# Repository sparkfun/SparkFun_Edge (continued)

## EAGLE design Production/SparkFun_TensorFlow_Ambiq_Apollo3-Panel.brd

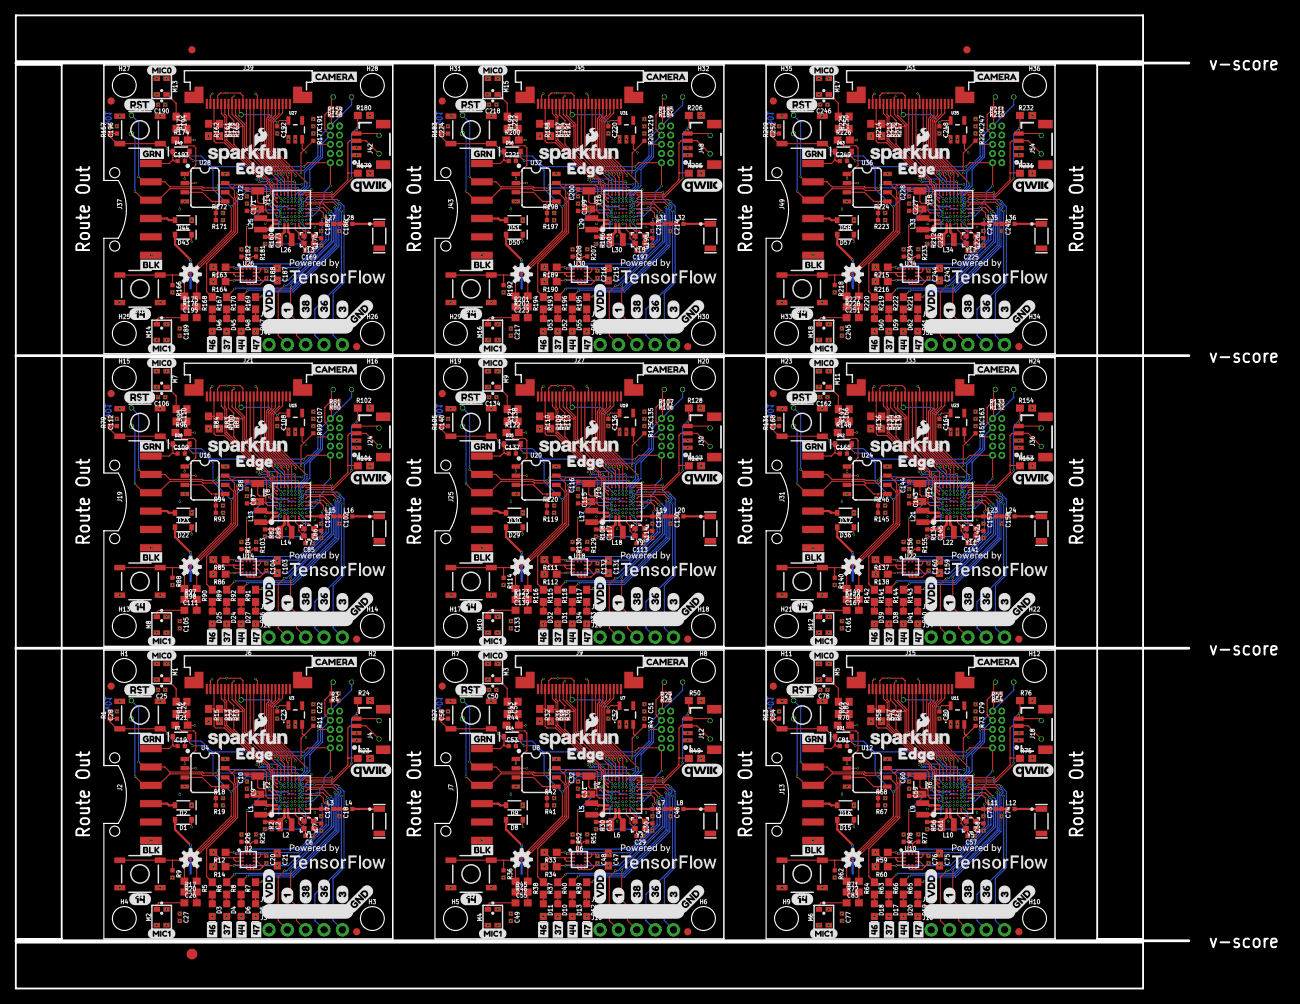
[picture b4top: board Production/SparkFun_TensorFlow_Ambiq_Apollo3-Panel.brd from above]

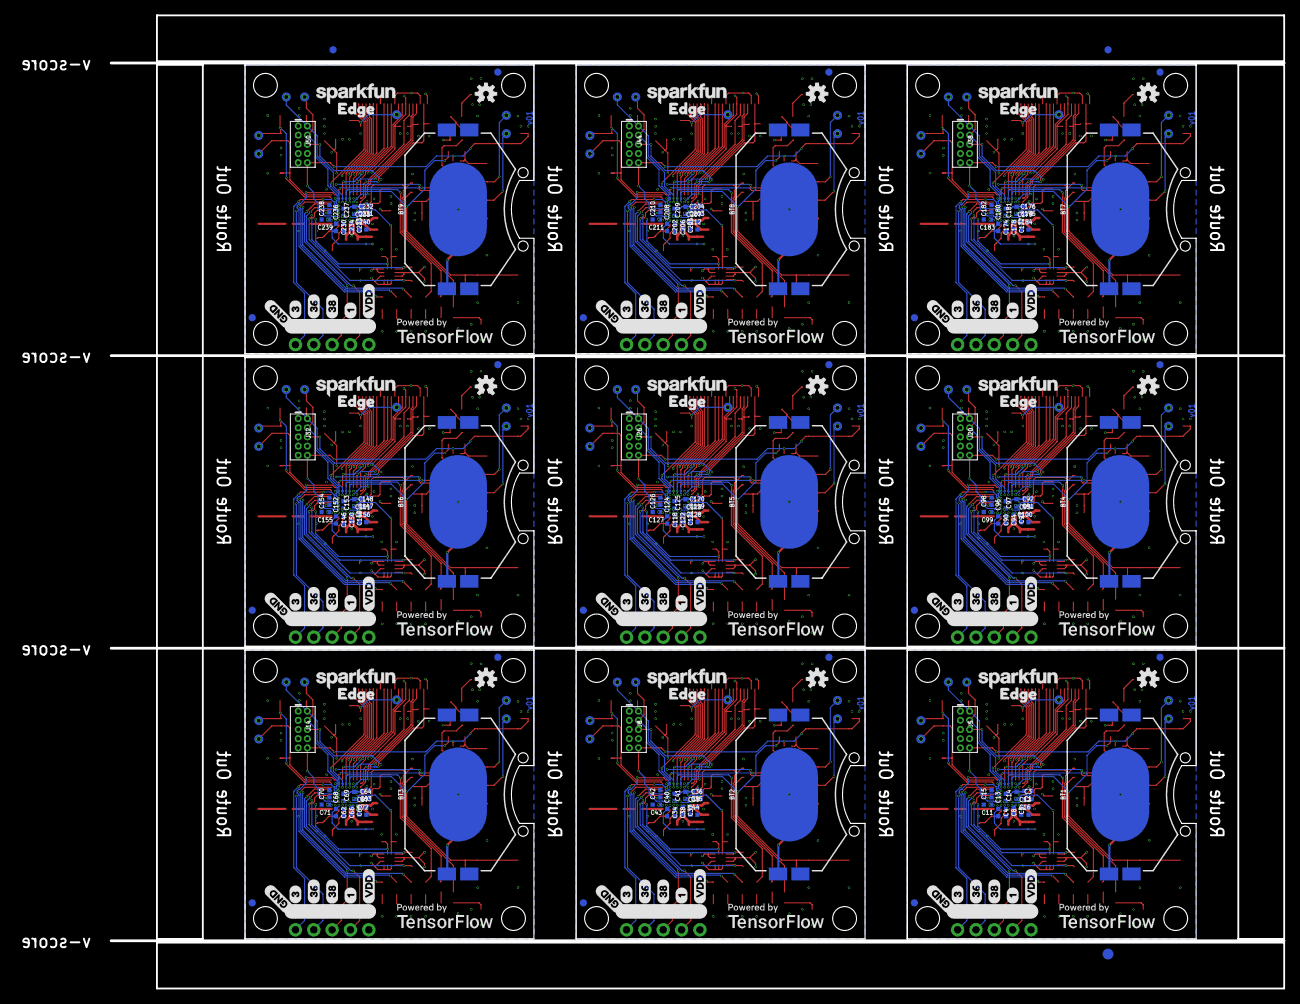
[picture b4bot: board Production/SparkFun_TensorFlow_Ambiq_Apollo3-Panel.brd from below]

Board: 4 copper layers, 162.4 x 134.7 mm, 1176 parts (291 on the bottom side), 666 nets.

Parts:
A1, A2, A3, A4, A5, A6, A7, A8, A9: 2.4GHZ-3.2X1.6MM; ANT-2.4GHZ-3.2X1.6X1.2MM
BT1, BT2, BT3, BT4, BT5, BT6, BT7, BT8, BT9: BATTCON_20MM_4LEGS_OVERPASTE_INNER
C1, C35, C63, C91, C119, C147, C175, C203, C231: 0.47uF; 0402-TIGHT
C2, C33, C61, C89, C117, C145, C173, C201, C229: 4.7uF; 0402-TIGHT
C3, C5, C8, C16, C36, C37, C38, C44, C64, C65, C66, C72, C92, C93, C94, C100, C120, C121, C122, C128, C148, C149, C150, C156, C176, C177, C178, C184, C204, C205, C206, C212, C232, C233, C234, C240: 2.2uF; 0402-TIGHT
C4, C12, C13, C14, C15, C22, C23, C34, C39, C40, C41, C42, C51, C52, C62, C67, C68, C69, C70, C79, C80, C90, C95, C96, C97, C98, C107, C108, C118, C123, C124, C125, C126, C135, C136, C146, C151, C152, C153, C154, C163, C164, C174, C179, C180, C181, C182, C191, C192, C202, C207, C208, C209, C210, C219, C220, C230, C235, C236, C237, C238, C247, C248: 1.0uF; 0402-TIGHT
C6, C7, C29, C30, C57, C58, C85, C86, C113, C114, C141, C142, C169, C170, C197, C198, C225, C226: 6pF; 0402-TIGHT
C9, C10, C31, C32, C59, C60, C87, C88, C115, C116, C143, C144, C171, C172, C199, C200, C227, C228: 15pF; 0402-TIGHT
C11, C43, C71, C99, C127, C155, C183, C211, C239: 47nF; 0402-TIGHT
C17, C45, C73, C101, C129, C157, C185, C213, C241: DNP; 0402-TIGHT
C18, C46, C74, C102, C130, C158, C186, C214, C242: 0.5pF; 0402-TIGHT
C19, C20, C25, C27, C48, C49, C50, C53, C76, C77, C78, C81, C104, C105, C106, C109, C132, C133, C134, C137, C160, C161, C162, C165, C188, C189, C190, C193, C216, C217, C218, C221, C244, C245, C246, C249: 0.1uF; 0402-TIGHT
C21, C47, C75, C103, C131, C159, C187, C215, C243: 10uF; 0603
C24, C26, C54, C55, C82, C83, C110, C111, C138, C139, C166, C167, C194, C195, C222, C223, C250, C251: 4.7uF; 0603
C28, C56, C84, C112, C140, C168, C196, C224, C252: 1.0nF; 0402-TIGHT
D1, D2, D8, D9, D15, D16, D22, D23, D29, D30, D36, D37, D43, D44, D50, D51, D57, D58: 1A/23V/620mV; SOD-323@1
D3, D11, D18, D25, D32, D39, D46, D53, D60: RED; LED-0603
D4, D10, D17, D24, D31, D38, D45, D52, D59: BLUE; LED-0603
D5, D12, D19, D26, D33, D40, D47, D54, D61: Yellow; LED-0603
D6, D13, D20, D27, D34, D41, D48, D55, D62: GREEN; LED-0603
D7, D14, D21, D28, D35, D42, D49, D56, D63: 250mA/100V; SOD-323
E$1, E$2, E$3, E$4: FIDUCIAL-1X2
E$5, E$6: FIDUCIAL-1.5X3
FD1, FD2, FD3, FD4, FD5, FD6, FD7, FD8, FD9, FD10, FD11, FD12, FD13, FD14, FD15, FD16, FD17, FD18, FD19, FD20, FD21, FD22, FD23, FD24, FD25, FD26, FD27, FD28, FD29, FD30, FD31, FD32, FD33, FD34, FD35, FD36: FIDUCIAL1X2; FIDUCIAL-1X2
H1, H2, H3, H4, H5, H6, H7, H8, H9, H10, H11, H12, H13, H14, H15, H16, H17, H18, H19, H20, H21, H22, H23, H24, H25, H26, H27, H28, H29, H30, H31, H32, H33, H34, H35, H36: STAND-OFF
J1, J3, J10, J11, J16, J17, J22, J23, J28, J29, J34, J35, J40, J41, J46, J47, J52, J53: 1X05_NO_SILK
J2, J7, J13, J19, J25, J31, J37, J43, J49: 1X06-SMD_RA_MALE
J4, J12, J18, J24, J30, J36, J42, J48, J54: 1X04_1MM_RA
J5, J8, J14, J20, J26, J32, J38, J44, J50: CORTEX_DEBUG_PTH; 2X5-PTH-1.27MM
J6, J9, J15, J21, J27, J33, J39, J45, J51: CAMERA-0V7670; FPC-24-AMPHENOL-SFV24R-1STE1HLF
L1, L5, L9, L13, L17, L21, L25, L29, L33: 2.2uH; 0805-WIDE
L2, L6, L10, L14, L18, L22, L26, L30, L34: 1.0uH; 0805-WIDE
L3, L7, L11, L15, L19, L23, L27, L31, L35: 2.7nH; 0402-TIGHT
L4, L8, L12, L16, L20, L24, L28, L32, L36: 2.0nH; 0402-TIGHT
LOGO1, LOGO3, LOGO5, LOGO7, LOGO9, LOGO11, LOGO13, LOGO15, LOGO17: SFE_LOGO_NAME_FLAME.1_INCH; SFE_LOGO_NAME_FLAME_.1
LOGO2, LOGO4, LOGO6, LOGO8, LOGO10, LOGO12, LOGO14, LOGO16, LOGO18: OSHW-LOGOS; OSHW-LOGO-S
M1, M2, M3, M4, M5, M6, M7, M8, M9, M10, M11, M12, M13, M14, M15, M16, M17, M18: MEMS_MIC; SPW2430HR5H-B
R1, R3, R4, R9, R10, R11, R19, R22, R25, R26, R27, R28, R29, R35, R36, R41, R47, R48, R51, R52, R53, R54, R55, R61, R62, R67, R73, R74, R77, R78, R79, R80, R81, R87, R88, R93, R99, R100, R103, R104, R105, R106, R107, R113, R114, R119, R125, R126, R129, R130, R131, R132, R133, R139, R140, R145, R151, R152, R155, R156, R157, R158, R159, R165, R166, R171, R177, R178, R181, R182, R183, R184, R185, R191, R192, R197, R203, R204, R207, R208, R209, R210, R211, R217, R218, R223, R229, R230, R233, R234: 10k; 0402-TIGHT
R2, R30, R56, R82, R108, R134, R160, R186, R212: 0; 0402-TIGHT
R5, R6, R7, R8, R37, R38, R39, R40, R63, R64, R65, R66, R89, R90, R91, R92, R115, R116, R117, R118, R141, R142, R143, R144, R167, R168, R169, R170, R193, R194, R195, R196, R219, R220, R221, R222: 1k; 0603
R12, R13, R14, R15, R23, R24, R31, R32, R33, R34, R49, R50, R57, R58, R59, R60, R75, R76, R83, R84, R85, R86, R101, R102, R109, R110, R111, R112, R127, R128, R135, R136, R137, R138, R153, R154, R161, R162, R163, R164, R179, R180, R187, R188, R189, R190, R205, R206, R213, R214, R215, R216, R231, R232: 4.7k; 0603
R16, R17, R43, R45, R69, R71, R95, R97, R121, R123, R147, R149, R173, R175, R199, R201, R225, R227: 10k; 0603
R18, R42, R68, R94, R120, R146, R172, R198, R224: 22k; 0402-TIGHT
R20, R21, R44, R46, R70, R72, R96, R98, R122, R124, R148, R150, R174, R176, R200, R202, R226, R228: 100k; 0603
S1, S2, S3, S4, S5, S6, S7, S8, S9, S10, S11, S12, S13, S14, S15, S16, S17, S18: TACTILE_SWITCH_SMD_5.2MM
TP1, TP2, TP3, TP4, TP5, TP6, TP7, TP8, TP9, TP10, TP11, TP12, TP13, TP14, TP15, TP16, TP17, TP18, TP19, TP20, TP21, TP22, TP23, TP24, TP25, TP26, TP27, TP28, TP29, TP30, TP31, TP32, TP33, TP34, TP35, TP36, TP37, TP38, TP39, TP40, TP41, TP42, TP43, TP44, TP45, TP46, TP47, TP48, TP49, TP50, TP51, TP52, TP53, TP54, TP55, TP56, TP57, TP58, TP59, TP60, TP61, TP62, TP63: TEST-POINT3X5; PAD.03X.05
U1, U5, U9, U13, U17, U21, U25, U29, U33: AMBIQ-APOLLO3KBR; BGA-81-5X5MM
U2, U6, U10, U14, U18, U22, U26, U30, U34: LIS2DH12; LGA-12-LISDH12
U3, U7, U11, U15, U19, U23, U27, U31, U35: 1.8V; SOT23-5
U4, U8, U12, U16, U20, U24, U28, U32, U36: LMV358; SO08
U$1, U$55, U$85, U$115, U$145, U$175, U$205, U$235, U$265: MIC00
U$2, U$41, U$71, U$101, U$131, U$161, U$191, U$221, U$251: BLK2
U$3, U$14, U$31, U$38, U$61, U$68, U$91, U$98, U$121, U$128, U$151, U$158, U$181, U$188, U$211, U$218, U$241, U$248: GND0
U$4, U$9, U$32, U$35, U$62, U$65, U$92, U$95, U$122, U$125, U$152, U$155, U$182, U$185, U$212, U$215, U$242, U$245: VDD1
U$5, U$8, U$43, U$44, U$73, U$74, U$103, U$104, U$133, U$134, U$163, U$164, U$193, U$194, U$223, U$224, U$253, U$254: 10
U$6, U$11, U$33, U$36, U$63, U$66, U$93, U$96, U$123, U$126, U$153, U$156, U$183, U$186, U$213, U$216, U$243, U$246: 383
U$7, U$12, U$34, U$37, U$64, U$67, U$94, U$97, U$124, U$127, U$154, U$157, U$184, U$187, U$214, U$217, U$244, U$247: 364
U$10, U$13, U$45, U$46, U$75, U$76, U$105, U$106, U$135, U$136, U$165, U$166, U$195, U$196, U$225, U$226, U$255, U$256: 31
U$15, U$47, U$77, U$107, U$137, U$167, U$197, U$227, U$257: 461
U$16, U$48, U$78, U$108, U$138, U$168, U$198, U$228, U$258: 372
U$17, U$49, U$79, U$109, U$139, U$169, U$199, U$229, U$259: 443
U$18, U$50, U$80, U$110, U$140, U$170, U$200, U$230, U$260: 470
U$19, U$51, U$81, U$111, U$141, U$171, U$201, U$231, U$261: QWIIC_COPYRIGHT_SMALL
U$20, U$52, U$82, U$112, U$142, U$172, U$202, U$232, U$262: CAMERA3
U$21, U$25, U$53, U$58, U$83, U$88, U$113, U$118, U$143, U$148, U$173, U$178, U$203, U$208, U$233, U$238, U$263, U$268: POWEREDBY_TF#JPG
U$22, U$56, U$86, U$116, U$146, U$176, U$206, U$236, U$266: MIC11
U$23, U$24, U$54, U$57, U$84, U$87, U$114, U$117, U$144, U$147, U$174, U$177, U$204, U$207, U$234, U$237, U$264, U$267: EDGE0
U$26, U$39, U$69, U$99, U$129, U$159, U$189, U$219, U$249: 1416
U$27, U$40, U$70, U$100, U$130, U$160, U$190, U$220, U$250: RST15
U$28, U$42, U$72, U$102, U$132, U$162, U$192, U$222, U$252: GRN1
U$29, U$59, U$89, U$119, U$149, U$179, U$209, U$239, U$269: SFE_LOGO_NAME_.1
U$30, U$60, U$90, U$120, U$150, U$180, U$210, U$240, U$270: OSHW-LOGO-S
Y1, Y3, Y5, Y7, Y9, Y11, Y13, Y15, Y17: 32MHz; CRYSTAL-SMD-2.0X1.6MM
Y2, Y4, Y6, Y8, Y10, Y12, Y14, Y16, Y18: 32.768kHz; CRYSTAL-SMD-3.2X1.5MM

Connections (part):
1.8V: C23.1, J6.10, TP7.P$1, U3.5
1.8V1: C52.1, J9.10, TP14.P$1, U7.5
1.8V2: C80.1, J15.10, TP21.P$1, U11.5
1.8V3: C108.1, J21.10, TP28.P$1, U15.5
1.8V4: C136.1, J27.10, TP35.P$1, U19.5
1.8V5: C164.1, J33.10, TP42.P$1, U23.5
1.8V6: C192.1, J39.10, TP49.P$1, U27.5
1.8V7: C220.1, J45.10, TP56.P$1, U31.5
1.8V8: C248.1, J51.10, TP63.P$1, U35.5
ADC_VREF: C1.1, U1.A6
ADC_VREF1: C35.1, U5.A6
ADC_VREF2: C63.1, U9.A6
ADC_VREF3: C91.1, U13.A6
ADC_VREF4: C119.1, U17.A6
ADC_VREF5: C147.1, U21.A6
ADC_VREF6: C175.1, U25.A6
ADC_VREF7: C203.1, U29.A6
ADC_VREF8: C231.1, U33.A6
AMBIQ_!RST: C19.2, C28.1, J5.10, R1.1, S2.3, S2.4, U1.G3
AMBIQ_!RST1: C53.2, C56.1, J8.10, R27.1, S4.3, S4.4, U5.G3
AMBIQ_!RST2: C81.2, C84.1, J14.10, R53.1, S6.3, S6.4, U9.G3
AMBIQ_!RST3: C109.2, C112.1, J20.10, R79.1, S8.3, S8.4, U13.G3
AMBIQ_!RST4: C137.2, C140.1, J26.10, R105.1, S10.3, S10.4, U17.G3
AMBIQ_!RST5: C165.2, C168.1, J32.10, R131.1, S12.3, S12.4, U21.G3
AMBIQ_!RST6: C193.2, C196.1, J38.10, R157.1, S14.3, S14.4, U25.G3
AMBIQ_!RST7: C221.2, C224.1, J44.10, R183.1, S16.3, S16.4, U29.G3
AMBIQ_!RST8: C249.2, C252.1, J50.10, R209.1, S18.3, S18.4, U33.G3
DTR: C19.1, D7.C, J2.1
DTR1: C53.1, D14.C, J7.1
DTR2: C81.1, D21.C, J13.1
DTR3: C109.1, D28.C, J19.1
DTR4: C137.1, D35.C, J25.1
DTR5: C165.1, D42.C, J31.1
DTR6: C193.1, D49.C, J37.1
DTR7: C221.1, D56.C, J43.1
DTR8: C249.1, D63.C, J49.1
DVDD: C11.1, U1.H3
DVDD1: C43.1, U5.H3
DVDD2: C71.1, U9.H3
DVDD3: C99.1, U13.H3
DVDD4: C127.1, U17.H3
DVDD5: C155.1, U21.H3
DVDD6: C183.1, U25.H3
DVDD7: C211.1, U29.H3
DVDD8: C239.1, U33.H3
FTDI_VCC: D2.A, J2.4
FTDI_VCC1: D9.A, J7.4
FTDI_VCC2: D16.A, J13.4
FTDI_VCC3: D23.A, J19.4
FTDI_VCC4: D30.A, J25.4
FTDI_VCC5: D37.A, J31.4
FTDI_VCC6: D44.A, J37.4
FTDI_VCC7: D51.A, J43.4
FTDI_VCC8: D58.A, J49.4
GND: BT1.2, C1.2, C2.2, C3.2, C4.2, C5.2, C6.1, C7.1, C8.2, C9.1, C10.1, C11.2, C12.2, C13.2, C14.2, C15.2, C16.2, C17.2, C18.2, C20.2, C21.2, C22.2, C23.2, C25.2, C27.2, C28.2, D3.C, D4.C, D5.C, D6.C, J1.1, J1.2, J1.3, J1.4, J1.5, J2.6, J4.1, J5.3, J5.5, J5.9, J6.2, J6.15, M1.2, M1.3, M2.2, M2.3, R4.1, R11.1, R19.1, R22.1, S1.1, S1.2, S2.1, S2.2, U1.B3, U1.C2, U1.E2, U1.E3, U1.F2, U1.H1, U1.H2, U1.J2, U2.5, U2.6, U2.7, U2.8, U3.2, U4.4
GND1: BT2.2, C29.1, C30.1, C31.1, C32.1, C33.2, C34.2, C35.2, C36.2, C37.2, C38.2, C39.2, C40.2, C41.2, C42.2, C43.2, C44.2, C45.2, C46.2, C47.2, C48.2, C49.2, C50.2, C51.2, C52.2, C56.2, D10.C, D11.C, D12.C, D13.C, J7.6, J8.3, J8.5, J8.9, J9.2, J9.15, J11.1, J11.2, J11.3, J11.4, J11.5, J12.1, M3.2, M3.3, M4.2, M4.3, R28.1, R41.1, R47.1, R48.1, S3.1, S3.2, S4.1, S4.2, U5.B3, U5.C2, U5.E2, U5.E3, U5.F2, U5.H1, U5.H2, U5.J2, U6.5, U6.6, U6.7, U6.8, U7.2, U8.4
GND2: BT3.2, C57.1, C58.1, C59.1, C60.1, C61.2, C62.2, C63.2, C64.2, C65.2, C66.2, C67.2, C68.2, C69.2, C70.2, C71.2, C72.2, C73.2, C74.2, C75.2, C76.2, C77.2, C78.2, C79.2, C80.2, C84.2, D17.C, D18.C, D19.C, D20.C, J13.6, J14.3, J14.5, J14.9, J15.2, J15.15, J17.1, J17.2, J17.3, J17.4, J17.5, J18.1, M5.2, M5.3, M6.2, M6.3, R54.1, R67.1, R73.1, R74.1, S5.1, S5.2, S6.1, S6.2, U9.B3, U9.C2, U9.E2, U9.E3, U9.F2, U9.H1, U9.H2, U9.J2, U10.5, U10.6, U10.7, U10.8, U11.2, U12.4
GND3: BT4.2, C85.1, C86.1, C87.1, C88.1, C89.2, C90.2, C91.2, C92.2, C93.2, C94.2, C95.2, C96.2, C97.2, C98.2, C99.2, C100.2, C101.2, C102.2, C103.2, C104.2, C105.2, C106.2, C107.2, C108.2, C112.2, D24.C, D25.C, D26.C, D27.C, J19.6, J20.3, J20.5, J20.9, J21.2, J21.15, J23.1, J23.2, J23.3, J23.4, J23.5, J24.1, M7.2, M7.3, M8.2, M8.3, R80.1, R93.1, R99.1, R100.1, S7.1, S7.2, S8.1, S8.2, U13.B3, U13.C2, U13.E2, U13.E3, U13.F2, U13.H1, U13.H2, U13.J2, U14.5, U14.6, U14.7, U14.8, U15.2, U16.4
GND4: BT5.2, C113.1, C114.1, C115.1, C116.1, C117.2, C118.2, C119.2, C120.2, C121.2, C122.2, C123.2, C124.2, C125.2, C126.2, C127.2, C128.2, C129.2, C130.2, C131.2, C132.2, C133.2, C134.2, C135.2, C136.2, C140.2, D31.C, D32.C, D33.C, D34.C, J25.6, J26.3, J26.5, J26.9, J27.2, J27.15, J29.1, J29.2, J29.3, J29.4, J29.5, J30.1, M9.2, M9.3, M10.2, M10.3, R106.1, R119.1, R125.1, R126.1, S9.1, S9.2, S10.1, S10.2, U17.B3, U17.C2, U17.E2, U17.E3, U17.F2, U17.H1, U17.H2, U17.J2, U18.5, U18.6, U18.7, U18.8, U19.2, U20.4
GND5: BT6.2, C141.1, C142.1, C143.1, C144.1, C145.2, C146.2, C147.2, C148.2, C149.2, C150.2, C151.2, C152.2, C153.2, C154.2, C155.2, C156.2, C157.2, C158.2, C159.2, C160.2, C161.2, C162.2, C163.2, C164.2, C168.2, D38.C, D39.C, D40.C, D41.C, J31.6, J32.3, J32.5, J32.9, J33.2, J33.15, J35.1, J35.2, J35.3, J35.4, J35.5, J36.1, M11.2, M11.3, M12.2, M12.3, R132.1, R145.1, R151.1, R152.1, S11.1, S11.2, S12.1, S12.2, U21.B3, U21.C2, U21.E2, U21.E3, U21.F2, U21.H1, U21.H2, U21.J2, U22.5, U22.6, U22.7, U22.8, U23.2, U24.4
GND6: BT7.2, C169.1, C170.1, C171.1, C172.1, C173.2, C174.2, C175.2, C176.2, C177.2, C178.2, C179.2, C180.2, C181.2, C182.2, C183.2, C184.2, C185.2, C186.2, C187.2, C188.2, C189.2, C190.2, C191.2, C192.2, C196.2, D45.C, D46.C, D47.C, D48.C, J37.6, J38.3, J38.5, J38.9, J39.2, J39.15, J41.1, J41.2, J41.3, J41.4, J41.5, J42.1, M13.2, M13.3, M14.2, M14.3, R158.1, R171.1, R177.1, R178.1, S13.1, S13.2, S14.1, S14.2, U25.B3, U25.C2, U25.E2, U25.E3, U25.F2, U25.H1, U25.H2, U25.J2, U26.5, U26.6, U26.7, U26.8, U27.2, U28.4
GND7: BT8.2, C197.1, C198.1, C199.1, C200.1, C201.2, C202.2, C203.2, C204.2, C205.2, C206.2, C207.2, C208.2, C209.2, C210.2, C211.2, C212.2, C213.2, C214.2, C215.2, C216.2, C217.2, C218.2, C219.2, C220.2, C224.2, D52.C, D53.C, D54.C, D55.C, J43.6, J44.3, J44.5, J44.9, J45.2, J45.15, J47.1, J47.2, J47.3, J47.4, J47.5, J48.1, M15.2, M15.3, M16.2, M16.3, R184.1, R197.1, R203.1, R204.1, S15.1, S15.2, S16.1, S16.2, U29.B3, U29.C2, U29.E2, U29.E3, U29.F2, U29.H1, U29.H2, U29.J2, U30.5, U30.6, U30.7, U30.8, U31.2, U32.4
GND8: BT9.2, C225.1, C226.1, C227.1, C228.1, C229.2, C230.2, C231.2, C232.2, C233.2, C234.2, C235.2, C236.2, C237.2, C238.2, C239.2, C240.2, C241.2, C242.2, C243.2, C244.2, C245.2, C246.2, C247.2, C248.2, C252.2, D59.C, D60.C, D61.C, D62.C, J49.6, J50.3, J50.5, J50.9, J51.2, J51.15, J53.1, J53.2, J53.3, J53.4, J53.5, J54.1, M17.2, M17.3, M18.2, M18.3, R210.1, R223.1, R229.1, R230.1, S17.1, S17.2, S18.1, S18.2, U33.B3, U33.C2, U33.E2, U33.E3, U33.F2, U33.H1, U33.H2, U33.J2, U34.5, U34.6, U34.7, U34.8, U35.2, U36.4
GPIO0/ACCEL_INT1: R51.2, U5.H4, U6.11
GPIO0/ACCEL_INT2: R25.2, U1.H4, U2.11
GPIO0/ACCEL_INT3: R77.2, U9.H4, U10.11
GPIO0/ACCEL_INT4: R103.2, U13.H4, U14.11
GPIO0/ACCEL_INT5: R129.2, U17.H4, U18.11
GPIO0/ACCEL_INT6: R155.2, U21.H4, U22.11
GPIO0/ACCEL_INT7: R181.2, U25.H4, U26.11
GPIO0/ACCEL_INT8: R207.2, U29.H4, U30.11
GPIO0/ACCEL_INT9: R233.2, U33.H4, U34.11
GPIO1_J3_1: J10.2, U5.G4
GPIO1_J3_2: J3.2, U1.G4
GPIO1_J3_3: J16.2, U9.G4
GPIO1_J3_4: J22.2, U13.G4
GPIO1_J3_5: J28.2, U17.G4
GPIO1_J3_6: J34.2, U21.G4
GPIO1_J3_7: J40.2, U25.G4
GPIO1_J3_8: J46.2, U29.G4
GPIO1_J3_9: J52.2, U33.G4
GPIO3_J3_1: J10.5, U5.G5
GPIO3_J3_2: J16.5, U9.G5
GPIO3_J3_3: J22.5, U13.G5
GPIO3_J3_4: J28.5, U17.G5
GPIO3_J3_5: J3.5, U1.G5
GPIO3_J3_6: J34.5, U21.G5
GPIO3_J3_7: J40.5, U25.G5
GPIO3_J3_8: J46.5, U29.G5
GPIO3_J3_9: J52.5, U33.G5
GPIO4/CAMERA_Y1: J9.18, U5.D9
GPIO4/CAMERA_Y2: J15.18, U9.D9
GPIO4/CAMERA_Y3: J21.18, U13.D9
GPIO4/CAMERA_Y4: J6.18, U1.D9
GPIO4/CAMERA_Y5: J27.18, U17.D9
GPIO4/CAMERA_Y6: J33.18, U21.D9
GPIO4/CAMERA_Y7: J39.18, U25.D9
GPIO4/CAMERA_Y8: J45.18, U29.D9
GPIO4/CAMERA_Y9: J51.18, U33.D9
GPIO5/CAMERA_Y1: J9.20, U5.E9
GPIO5/CAMERA_Y2: J15.20, U9.E9
GPIO5/CAMERA_Y3: J6.20, U1.E9
GPIO5/CAMERA_Y4: J21.20, U13.E9
GPIO5/CAMERA_Y5: J27.20, U17.E9
GPIO5/CAMERA_Y6: J33.20, U21.E9
GPIO5/CAMERA_Y7: J39.20, U25.E9
GPIO5/CAMERA_Y8: J45.20, U29.E9
GPIO5/CAMERA_Y9: J51.20, U33.E9
GPIO6/CAMERA_Y0: J6.19, U1.E8
GPIO6/CAMERA_Y1: J9.19, U5.E8
GPIO6/CAMERA_Y2: J15.19, U9.E8
GPIO6/CAMERA_Y3: J21.19, U13.E8
GPIO6/CAMERA_Y4: J27.19, U17.E8
GPIO6/CAMERA_Y5: J33.19, U21.E8
GPIO6/CAMERA_Y6: J39.19, U25.E8
GPIO6/CAMERA_Y7: J45.19, U29.E8
GPIO6/CAMERA_Y8: J51.19, U33.E8
GPIO7/CAM_XCLK: J6.13, U1.F9
GPIO7/CAM_XCLK1: J9.13, U5.F9
GPIO7/CAM_XCLK2: J15.13, U9.F9
GPIO7/CAM_XCLK3: J21.13, U13.F9
GPIO7/CAM_XCLK4: J27.13, U17.F9
GPIO7/CAM_XCLK5: J33.13, U21.F9
GPIO7/CAM_XCLK6: J39.13, U25.F9
GPIO7/CAM_XCLK7: J45.13, U29.F9
GPIO7/CAM_XCLK8: J51.13, U33.F9
GPIO8/CAMERA_Y1: J6.21, U1.F8
GPIO8/CAMERA_Y2: J9.21, U5.F8
GPIO8/CAMERA_Y3: J15.21, U9.F8
GPIO8/CAMERA_Y4: J21.21, U13.F8
GPIO8/CAMERA_Y5: J27.21, U17.F8
GPIO8/CAMERA_Y6: J33.21, U21.F8
GPIO8/CAMERA_Y7: J39.21, U25.F8
GPIO8/CAMERA_Y8: J45.21, U29.F8
GPIO8/CAMERA_Y9: J51.21, U33.F8
GPIO9/CAMERA_Y1: J9.22, U5.G7
GPIO9/CAMERA_Y2: J6.22, U1.G7
GPIO9/CAMERA_Y3: J15.22, U9.G7
GPIO9/CAMERA_Y4: J21.22, U13.G7
GPIO9/CAMERA_Y5: J27.22, U17.G7
GPIO9/CAMERA_Y6: J33.22, U21.G7
GPIO9/CAMERA_Y7: J39.22, U25.G7
GPIO9/CAMERA_Y8: J45.22, U29.G7
GPIO9/CAMERA_Y9: J51.22, U33.G7
GPIO10/CAMERA_DVDD_EN: R11.2, U1.G8, U3.3
GPIO10/CAMERA_DVDD_EN1: R47.2, U5.G8, U7.3
GPIO10/CAMERA_DVDD_EN2: R73.2, U9.G8, U11.3
GPIO10/CAMERA_DVDD_EN3: R99.2, U13.G8, U15.3
GPIO10/CAMERA_DVDD_EN4: R125.2, U17.G8, U19.3
GPIO10/CAMERA_DVDD_EN5: R151.2, U21.G8, U23.3
GPIO10/CAMERA_DVDD_EN6: R177.2, U25.G8, U27.3
GPIO10/CAMERA_DVDD_EN7: R203.2, U29.G8, U31.3
GPIO10/CAMERA_DVDD_EN8: R229.2, U33.G8, U35.3
GPIO11/MIC0: R21.1, U1.B5, U4.1
GPIO11/MIC1: R44.1, U5.B5, U8.1
GPIO11/MIC2: R70.1, U9.B5, U12.1
GPIO11/MIC3: R96.1, U13.B5, U16.1
GPIO11/MIC4: R122.1, U17.B5, U20.1
GPIO11/MIC5: R148.1, U21.B5, U24.1
GPIO11/MIC6: R174.1, U25.B5, U28.1
GPIO11/MIC7: R200.1, U29.B5, U32.1
GPIO11/MIC8: R226.1, U33.B5, U36.1
GPIO12/CAMERA_VSYNC: J6.7, U1.A7
GPIO12/CAMERA_VSYNC1: J9.7, U5.A7
GPIO12/CAMERA_VSYNC2: J15.7, U9.A7
GPIO12/CAMERA_VSYNC3: J21.7, U13.A7
GPIO12/CAMERA_VSYNC4: J27.7, U17.A7
GPIO12/CAMERA_VSYNC5: J33.7, U21.A7
GPIO12/CAMERA_VSYNC6: J39.7, U25.A7
GPIO12/CAMERA_VSYNC7: J45.7, U29.A7
GPIO12/CAMERA_VSYNC8: J51.7, U33.A7
GPIO13/CAMERA_PWDN: J6.8, R22.2, U1.B7
GPIO13/CAMERA_PWDN1: J9.8, R48.2, U5.B7
GPIO13/CAMERA_PWDN2: J15.8, R74.2, U9.B7
GPIO13/CAMERA_PWDN3: J21.8, R100.2, U13.B7
GPIO13/CAMERA_PWDN4: J27.8, R126.2, U17.B7
GPIO13/CAMERA_PWDN5: J33.8, R152.2, U21.B7
GPIO13/CAMERA_PWDN6: J39.8, R178.2, U25.B7
GPIO13/CAMERA_PWDN7: J45.8, R204.2, U29.B7
GPIO13/CAMERA_PWDN8: J51.8, R230.2, U33.B7
GPIO14/USER_BUTTON: D7.A, R9.1, S1.3, S1.4, U1.D7
GPIO14/USER_BUTTON1: D14.A, R36.1, S3.3, S3.4, U5.D7
GPIO14/USER_BUTTON2: D21.A, R62.1, S5.3, S5.4, U9.D7
GPIO14/USER_BUTTON3: D28.A, R88.1, S7.3, S7.4, U13.D7
GPIO14/USER_BUTTON4: D35.A, R114.1, S9.3, S9.4, U17.D7
GPIO14/USER_BUTTON5: D42.A, R140.1, S11.3, S11.4, U21.D7
GPIO14/USER_BUTTON6: D49.A, R166.1, S13.3, S13.4, U25.D7
GPIO14/USER_BUTTON7: D56.A, R192.1, S15.3, S15.4, U29.D7
GPIO14/USER_BUTTON8: D63.A, R218.1, S17.3, S17.4, U33.D7
GPIO15/CAMERA_RESET: J6.6, R10.1, U1.C7
GPIO15/CAMERA_RESET1: J9.6, R35.1, U5.C7
GPIO15/CAMERA_RESET2: J15.6, R61.1, U9.C7
GPIO15/CAMERA_RESET3: J21.6, R87.1, U13.C7
GPIO15/CAMERA_RESET4: J27.6, R113.1, U17.C7
GPIO15/CAMERA_RESET5: J33.6, R139.1, U21.C7
GPIO15/CAMERA_RESET6: J39.6, R165.1, U25.C7
GPIO15/CAMERA_RESET7: J45.6, R191.1, U29.C7
GPIO15/CAMERA_RESET8: J51.6, R217.1, U33.C7
GPIO17/ACCEL_INT1: R26.2, U1.D3, U2.12
GPIO17/ACCEL_INT2: R52.2, U5.D3, U6.12
GPIO17/ACCEL_INT3: R78.2, U9.D3, U10.12
GPIO17/ACCEL_INT4: R104.2, U13.D3, U14.12
GPIO17/ACCEL_INT5: R130.2, U17.D3, U18.12
GPIO17/ACCEL_INT6: R156.2, U21.D3, U22.12
GPIO17/ACCEL_INT7: R182.2, U25.D3, U26.12
GPIO17/ACCEL_INT8: R208.2, U29.D3, U30.12
GPIO17/ACCEL_INT9: R234.2, U33.D3, U34.12
GPIO20/SWDCK: J5.4, R4.2, TP1.P$1, U1.G6
GPIO20/SWDCK1: J8.4, R28.2, TP8.P$1, U5.G6
GPIO20/SWDCK2: J14.4, R54.2, TP15.P$1, U9.G6
GPIO20/SWDCK3: J20.4, R80.2, TP22.P$1, U13.G6
GPIO20/SWDCK4: J26.4, R106.2, TP29.P$1, U17.G6
GPIO20/SWDCK5: J32.4, R132.2, TP36.P$1, U21.G6
GPIO20/SWDCK6: J38.4, R158.2, TP43.P$1, U25.G6
GPIO20/SWDCK7: J44.4, R184.2, TP50.P$1, U29.G6
GPIO20/SWDCK8: J50.4, R210.2, TP57.P$1, U33.G6
GPIO21/SWDIO: J5.2, R3.1, TP2.P$1, U1.F7
GPIO21/SWDIO1: J8.2, R29.1, TP9.P$1, U5.F7
GPIO21/SWDIO2: J14.2, R55.1, TP16.P$1, U9.F7
GPIO21/SWDIO3: J20.2, R81.1, TP23.P$1, U13.F7
GPIO21/SWDIO4: J26.2, R107.1, TP30.P$1, U17.F7
GPIO21/SWDIO5: J32.2, R133.1, TP37.P$1, U21.F7
GPIO21/SWDIO6: J38.2, R159.1, TP44.P$1, U25.F7
GPIO21/SWDIO7: J44.2, R185.1, TP51.P$1, U29.F7
GPIO21/SWDIO8: J50.2, R211.1, TP58.P$1, U33.F7
GPIO22/CAMERA_Y1: J9.16, U5.C9
GPIO22/CAMERA_Y2: J15.16, U9.C9
GPIO22/CAMERA_Y3: J21.16, U13.C9
GPIO22/CAMERA_Y4: J27.16, U17.C9
GPIO22/CAMERA_Y5: J6.16, U1.C9
GPIO22/CAMERA_Y6: J33.16, U21.C9
GPIO22/CAMERA_Y7: J39.16, U25.C9
GPIO22/CAMERA_Y8: J45.16, U29.C9
GPIO22/CAMERA_Y9: J51.16, U33.C9
GPIO23/CAMERA_PCLK: J6.17, U1.D8
GPIO23/CAMERA_PCLK1: J9.17, U5.D8
GPIO23/CAMERA_PCLK2: J15.17, U9.D8
GPIO23/CAMERA_PCLK3: J21.17, U13.D8
GPIO23/CAMERA_PCLK4: J27.17, U17.D8
GPIO23/CAMERA_PCLK5: J33.17, U21.D8
GPIO23/CAMERA_PCLK6: J39.17, U25.D8
GPIO23/CAMERA_PCLK7: J45.17, U29.D8
GPIO23/CAMERA_PCLK8: J51.17, U33.D8
GPIO24/CAMERA_Y1: J9.14, U5.C8
GPIO24/CAMERA_Y2: J15.14, U9.C8
GPIO24/CAMERA_Y3: J21.14, U13.C8
GPIO24/CAMERA_Y4: J27.14, U17.C8
GPIO24/CAMERA_Y5: J33.14, U21.C8
GPIO24/CAMERA_Y6: J6.14, U1.C8
GPIO24/CAMERA_Y7: J39.14, U25.C8
GPIO24/CAMERA_Y8: J45.14, U29.C8
GPIO24/CAMERA_Y9: J51.14, U33.C8
GPIO25/I2C_SDA_CAMERA: J6.3, R15.1, U1.A8
GPIO25/I2C_SDA_CAMERA1: J9.3, R32.1, U5.A8
GPIO25/I2C_SDA_CAMERA2: J15.3, R58.1, U9.A8
GPIO25/I2C_SDA_CAMERA3: J21.3, R84.1, U13.A8
GPIO25/I2C_SDA_CAMERA4: J27.3, R110.1, U17.A8
GPIO25/I2C_SDA_CAMERA5: J33.3, R136.1, U21.A8
GPIO25/I2C_SDA_CAMERA6: J39.3, R162.1, U25.A8
GPIO25/I2C_SDA_CAMERA7: J45.3, R188.1, U29.A8
GPIO25/I2C_SDA_CAMERA8: J51.3, R214.1, U33.A8
GPIO26/CAMERA_HREF: J6.9, U1.B8
GPIO26/CAMERA_HREF1: J9.9, U5.B8
GPIO26/CAMERA_HREF2: J15.9, U9.B8
GPIO26/CAMERA_HREF3: J21.9, U13.B8
GPIO26/CAMERA_HREF4: J27.9, U17.B8
GPIO26/CAMERA_HREF5: J33.9, U21.B8
GPIO26/CAMERA_HREF6: J39.9, U25.B8
GPIO26/CAMERA_HREF7: J45.9, U29.B8
GPIO26/CAMERA_HREF8: J51.9, U33.B8
GPIO27/I2C_SCL_CAMERA: J6.5, R13.1, U1.B9
GPIO27/I2C_SCL_CAMERA1: J9.5, R31.1, U5.B9
GPIO27/I2C_SCL_CAMERA2: J15.5, R57.1, U9.B9
GPIO27/I2C_SCL_CAMERA3: J21.5, R83.1, U13.B9
GPIO27/I2C_SCL_CAMERA4: J27.5, R109.1, U17.B9
GPIO27/I2C_SCL_CAMERA5: J33.5, R135.1, U21.B9
GPIO27/I2C_SCL_CAMERA6: J39.5, R161.1, U25.B9
GPIO27/I2C_SCL_CAMERA7: J45.5, R187.1, U29.B9
GPIO27/I2C_SCL_CAMERA8: J51.5, R213.1, U33.B9
GPIO28/CAMERA_Y1: J9.12, U5.A9
GPIO28/CAMERA_Y2: J15.12, U9.A9
GPIO28/CAMERA_Y3: J21.12, U13.A9
GPIO28/CAMERA_Y4: J27.12, U17.A9
GPIO28/CAMERA_Y5: J33.12, U21.A9
GPIO28/CAMERA_Y6: J39.12, U25.A9
GPIO28/CAMERA_Y7: J6.12, U1.A9
GPIO28/CAMERA_Y8: J45.12, U29.A9
GPIO28/CAMERA_Y9: J51.12, U33.A9
GPIO29/MIC1: R20.1, U1.A5, U4.7
GPIO29/MIC2: R46.1, U5.A5, U8.7
GPIO29/MIC3: R72.1, U9.A5, U12.7
GPIO29/MIC4: R98.1, U13.A5, U16.7
GPIO29/MIC5: R124.1, U17.A5, U20.7
GPIO29/MIC6: R150.1, U21.A5, U24.7
GPIO29/MIC7: R176.1, U25.A5, U28.7
GPIO29/MIC8: R202.1, U29.A5, U32.7
GPIO29/MIC9: R228.1, U33.A5, U36.7
GPIO33/SWO: J5.6, U1.B6
GPIO33/SWO1: J8.6, U5.B6
GPIO33/SWO2: J14.6, U9.B6
GPIO33/SWO3: J20.6, U13.B6
GPIO33/SWO4: J26.6, U17.B6
GPIO33/SWO5: J32.6, U21.B6
GPIO33/SWO6: J38.6, U25.B6
GPIO33/SWO7: J44.6, U29.B6
GPIO33/SWO8: J50.6, U33.B6
GPIO36_J3_1: J10.4, U5.H6
GPIO36_J3_2: J16.4, U9.H6
GPIO36_J3_3: J22.4, U13.H6
GPIO36_J3_4: J3.4, U1.H6
GPIO36_J3_5: J28.4, U17.H6
GPIO36_J3_6: J34.4, U21.H6
GPIO36_J3_7: J40.4, U25.H6
GPIO36_J3_8: J46.4, U29.H6
GPIO36_J3_9: J52.4, U33.H6
GPIO37_LED_BLUE: R6.2, U1.H7
GPIO37_LED_BLUE1: R37.2, U5.H7
GPIO37_LED_BLUE2: R63.2, U9.H7
GPIO37_LED_BLUE3: R89.2, U13.H7
GPIO37_LED_BLUE4: R115.2, U17.H7
GPIO37_LED_BLUE5: R141.2, U21.H7
GPIO37_LED_BLUE6: R167.2, U25.H7
GPIO37_LED_BLUE7: R193.2, U29.H7
GPIO37_LED_BLUE8: R219.2, U33.H7
GPIO38_J3_1: J10.3, U5.J6
GPIO38_J3_2: J16.3, U9.J6
GPIO38_J3_3: J3.3, U1.J6
GPIO38_J3_4: J22.3, U13.J6
GPIO38_J3_5: J28.3, U17.J6
GPIO38_J3_6: J34.3, U21.J6
GPIO38_J3_7: J40.3, U25.J6
GPIO38_J3_8: J46.3, U29.J6
GPIO38_J3_9: J52.3, U33.J6
GPIO39_QWIIC_SCK: J4.4, R24.1, TP3.P$1, U1.J8
GPIO39_QWIIC_SCK1: J12.4, R50.1, TP10.P$1, U5.J8
GPIO39_QWIIC_SCK2: J18.4, R76.1, TP17.P$1, U9.J8
GPIO39_QWIIC_SCK3: J24.4, R102.1, TP24.P$1, U13.J8
GPIO39_QWIIC_SCK4: J30.4, R128.1, TP31.P$1, U17.J8
GPIO39_QWIIC_SCK5: J36.4, R154.1, TP38.P$1, U21.J8
GPIO39_QWIIC_SCK6: J42.4, R180.1, TP45.P$1, U25.J8
GPIO39_QWIIC_SCK7: J48.4, R206.1, TP52.P$1, U29.J8
GPIO39_QWIIC_SCK8: J54.4, R232.1, TP59.P$1, U33.J8
GPIO40_QWIIC_SDA: J4.3, R23.1, TP4.P$1, U1.J9
GPIO40_QWIIC_SDA1: J12.3, R49.1, TP11.P$1, U5.J9
GPIO40_QWIIC_SDA2: J18.3, R75.1, TP18.P$1, U9.J9
GPIO40_QWIIC_SDA3: J24.3, R101.1, TP25.P$1, U13.J9
GPIO40_QWIIC_SDA4: J30.3, R127.1, TP32.P$1, U17.J9
GPIO40_QWIIC_SDA5: J36.3, R153.1, TP39.P$1, U21.J9
GPIO40_QWIIC_SDA6: J42.3, R179.1, TP46.P$1, U25.J9
GPIO40_QWIIC_SDA7: J48.3, R205.1, TP53.P$1, U29.J9
GPIO40_QWIIC_SDA8: J54.3, R231.1, TP60.P$1, U33.J9
GPIO42/I2C_SCLK: R12.1, U1.H5, U2.1
GPIO42/I2C_SCLK1: R33.1, U5.H5, U6.1
GPIO42/I2C_SCLK2: R59.1, U9.H5, U10.1
GPIO42/I2C_SCLK3: R85.1, U13.H5, U14.1
GPIO42/I2C_SCLK4: R111.1, U17.H5, U18.1
GPIO42/I2C_SCLK5: R137.1, U21.H5, U22.1
GPIO42/I2C_SCLK6: R163.1, U25.H5, U26.1
GPIO42/I2C_SCLK7: R189.1, U29.H5, U30.1
GPIO42/I2C_SCLK8: R215.1, U33.H5, U34.1
GPIO43/I2C_SDA: R14.1, U1.J5, U2.4
GPIO43/I2C_SDA1: R34.1, U5.J5, U6.4
GPIO43/I2C_SDA2: R60.1, U9.J5, U10.4
GPIO43/I2C_SDA3: R86.1, U13.J5, U14.4
GPIO43/I2C_SDA4: R112.1, U17.J5, U18.4
GPIO43/I2C_SDA5: R138.1, U21.J5, U22.4
GPIO43/I2C_SDA6: R164.1, U25.J5, U26.4
GPIO43/I2C_SDA7: R190.1, U29.J5, U30.4
GPIO43/I2C_SDA8: R216.1, U33.J5, U34.4
GPIO44/LED_GREEN: R8.2, U1.J7
GPIO44/LED_GREEN1: R40.2, U5.J7
GPIO44/LED_GREEN2: R66.2, U9.J7
GPIO44/LED_GREEN3: R92.2, U13.J7
GPIO44/LED_GREEN4: R118.2, U17.J7
GPIO44/LED_GREEN5: R144.2, U21.J7
GPIO44/LED_GREEN6: R170.2, U25.J7
GPIO44/LED_GREEN7: R196.2, U29.J7
GPIO44/LED_GREEN8: R222.2, U33.J7
GPIO46/LED_RED: R5.2, U1.E7
GPIO46/LED_RED1: R38.2, U5.E7
GPIO46/LED_RED2: R64.2, U9.E7
GPIO46/LED_RED3: R90.2, U13.E7
GPIO46/LED_RED4: R116.2, U17.E7
GPIO46/LED_RED5: R142.2, U21.E7
GPIO46/LED_RED6: R168.2, U25.E7
GPIO46/LED_RED7: R194.2, U29.E7
GPIO46/LED_RED8: R220.2, U33.E7
GPIO47/LED_YELLOW: R7.2, U1.H9
GPIO47/LED_YELLOW1: R39.2, U5.H9
GPIO47/LED_YELLOW2: R65.2, U9.H9
GPIO47/LED_YELLOW3: R91.2, U13.H9
GPIO47/LED_YELLOW4: R117.2, U17.H9
GPIO47/LED_YELLOW5: R143.2, U21.H9
GPIO47/LED_YELLOW6: R169.2, U25.H9
GPIO47/LED_YELLOW7: R195.2, U29.H9
GPIO47/LED_YELLOW8: R221.2, U33.H9
MIC0_OUT: C24.1, M1.1
MIC0_OUT1: C54.1, M3.1
MIC0_OUT2: C82.1, M5.1
MIC0_OUT3: C110.1, M7.1
MIC0_OUT4: C138.1, M9.1
MIC0_OUT5: C166.1, M11.1
MIC0_OUT6: C194.1, M13.1
MIC0_OUT7: C222.1, M15.1
MIC0_OUT8: C250.1, M17.1
MIC1_OUT: C26.1, M2.1
MIC1_OUT1: C55.1, M4.1
MIC1_OUT2: C83.1, M6.1
MIC1_OUT3: C111.1, M8.1
MIC1_OUT4: C139.1, M10.1
MIC1_OUT5: C167.1, M12.1
MIC1_OUT6: C195.1, M14.1
MIC1_OUT7: C223.1, M16.1
MIC1_OUT8: C251.1, M18.1
unnamed: A1.FEED, L4.2
unnamed: C7.2, U1.G1, Y1.1
unnamed: C6.2, U1.F1, Y1.3
unnamed: C30.2, U5.G1, Y3.1
unnamed: D4.A, R6.1
unnamed: D3.A, R5.1
unnamed: D5.A, R7.1
unnamed: D6.A, R8.1
unnamed: R18.1, R19.2, U4.3, U4.5
unnamed: C24.2, R16.2
unnamed: R17.1, R20.2, U4.6
unnamed: R16.1, R21.2, U4.2
unnamed: C29.2, U5.F1, Y3.3
unnamed: C26.2, R17.2
unnamed: C46.1, L7.2, L8.1
unnamed: C18.1, L3.2, L4.1
unnamed: A2.FEED, L8.2
unnamed: D10.A, R37.1
unnamed: D11.A, R38.1
unnamed: D12.A, R39.1
unnamed: D13.A, R40.1
unnamed: R41.2, R42.1, U8.3, U8.5
unnamed: C54.2, R43.2
unnamed: R43.1, R44.2, U8.2
unnamed: R45.1, R46.2, U8.6
unnamed: C55.2, R45.2
unnamed: C58.2, U9.G1, Y5.1
unnamed: C57.2, U9.F1, Y5.3
unnamed: C74.1, L11.2, L12.1
unnamed: A3.FEED, L12.2
unnamed: D17.A, R63.1
unnamed: D18.A, R64.1
unnamed: D19.A, R65.1
unnamed: D20.A, R66.1
unnamed: R67.2, R68.1, U12.3, U12.5
unnamed: C82.2, R69.2
unnamed: R69.1, R70.2, U12.2
unnamed: R71.1, R72.2, U12.6
unnamed: C83.2, R71.2
unnamed: C86.2, U13.G1, Y7.1
unnamed: C85.2, U13.F1, Y7.3
unnamed: C102.1, L15.2, L16.1
unnamed: A4.FEED, L16.2
unnamed: D24.A, R89.1
unnamed: D25.A, R90.1
unnamed: D26.A, R91.1
unnamed: D27.A, R92.1
unnamed: R93.2, R94.1, U16.3, U16.5
unnamed: C110.2, R95.2
unnamed: R95.1, R96.2, U16.2
unnamed: R97.1, R98.2, U16.6
unnamed: C111.2, R97.2
unnamed: C114.2, U17.G1, Y9.1
unnamed: C113.2, U17.F1, Y9.3
unnamed: C130.1, L19.2, L20.1
unnamed: A5.FEED, L20.2
unnamed: D31.A, R115.1
unnamed: D32.A, R116.1
unnamed: D33.A, R117.1
unnamed: D34.A, R118.1
unnamed: R119.2, R120.1, U20.3, U20.5
unnamed: C138.2, R121.2
unnamed: R121.1, R122.2, U20.2
unnamed: R123.1, R124.2, U20.6
unnamed: C139.2, R123.2
unnamed: C142.2, U21.G1, Y11.1
unnamed: C141.2, U21.F1, Y11.3
unnamed: C158.1, L23.2, L24.1
unnamed: A6.FEED, L24.2
unnamed: D38.A, R141.1
unnamed: D39.A, R142.1
unnamed: D40.A, R143.1
unnamed: D41.A, R144.1
unnamed: R145.2, R146.1, U24.3, U24.5
unnamed: C166.2, R147.2
unnamed: R147.1, R148.2, U24.2
unnamed: R149.1, R150.2, U24.6
unnamed: C167.2, R149.2
unnamed: C170.2, U25.G1, Y13.1
unnamed: C169.2, U25.F1, Y13.3
unnamed: C186.1, L27.2, L28.1
unnamed: A7.FEED, L28.2
unnamed: D45.A, R167.1
unnamed: D46.A, R168.1
unnamed: D47.A, R169.1
unnamed: D48.A, R170.1
unnamed: R171.2, R172.1, U28.3, U28.5
unnamed: C194.2, R173.2
unnamed: R173.1, R174.2, U28.2
unnamed: R175.1, R176.2, U28.6
unnamed: C195.2, R175.2
unnamed: C198.2, U29.G1, Y15.1
unnamed: C197.2, U29.F1, Y15.3
unnamed: C214.1, L31.2, L32.1
unnamed: A8.FEED, L32.2
unnamed: D52.A, R193.1
unnamed: D53.A, R194.1
unnamed: D54.A, R195.1
unnamed: D55.A, R196.1
unnamed: R197.2, R198.1, U32.3, U32.5
unnamed: C222.2, R199.2
unnamed: R199.1, R200.2, U32.2
unnamed: R201.1, R202.2, U32.6
unnamed: C223.2, R201.2
unnamed: C226.2, U33.G1, Y17.1
unnamed: C225.2, U33.F1, Y17.3
unnamed: C242.1, L35.2, L36.1
unnamed: A9.FEED, L36.2
unnamed: D59.A, R219.1
unnamed: D60.A, R220.1
unnamed: D61.A, R221.1
unnamed: D62.A, R222.1
unnamed: R223.2, R224.1, U36.3, U36.5
unnamed: C250.2, R225.2
unnamed: R225.1, R226.2, U36.2
unnamed: R227.1, R228.2, U36.6
unnamed: C251.2, R227.2
RFIOP: C17.1, L3.1, U1.J1
RFIOP1: C45.1, L7.1, U5.J1
RFIOP2: C73.1, L11.1, U9.J1
RFIOP3: C101.1, L15.1, U13.J1
RFIOP4: C129.1, L19.1, U17.J1
RFIOP5: C157.1, L23.1, U21.J1
RFIOP6: C185.1, L27.1, U25.J1
RFIOP7: C213.1, L31.1, U29.J1
RFIOP8: C241.1, L35.1, U33.J1
SIMBUCK_SWSEL: L1.2, U1.A2
SIMBUCK_SWSEL1: L5.2, U5.A2
SIMBUCK_SWSEL2: L9.2, U9.A2
SIMBUCK_SWSEL3: L13.2, U13.A2
SIMBUCK_SWSEL4: L17.2, U17.A2
SIMBUCK_SWSEL5: L21.2, U21.A2
SIMBUCK_SWSEL6: L25.2, U25.A2
SIMBUCK_SWSEL7: L29.2, U29.A2
SIMBUCK_SWSEL8: L33.2, U33.A2
SIMOBUCK_SW: L1.1, U1.A1
SIMOBUCK_SW1: L5.1, U5.A1
SIMOBUCK_SW2: L9.1, U9.A1
SIMOBUCK_SW3: L13.1, U13.A1
SIMOBUCK_SW4: L17.1, U17.A1
SIMOBUCK_SW5: L21.1, U21.A1
SIMOBUCK_SW6: L25.1, U25.A1
SIMOBUCK_SW7: L29.1, U29.A1
SIMOBUCK_SW8: L33.1, U33.A1
UART-RX/GPIO1: J7.3, TP13.P$1, U5.H8
UART-RX/GPIO2: J13.3, TP20.P$1, U9.H8
UART-RX/GPIO3: J19.3, TP27.P$1, U13.H8
UART-RX/GPIO4: J25.3, TP34.P$1, U17.H8
UART-RX/GPIO5: J31.3, TP41.P$1, U21.H8
UART-RX/GPIO6: J37.3, TP48.P$1, U25.H8
UART-RX/GPIO7: J43.3, TP55.P$1, U29.H8
UART-RX/GPIO8: J49.3, TP62.P$1, U33.H8
UART-RX/GPIO49: J2.3, TP6.P$1, U1.H8
UART-TX/GPIO1: J7.2, TP12.P$1, U5.G9
UART-TX/GPIO2: J13.2, TP19.P$1, U9.G9
UART-TX/GPIO3: J19.2, TP26.P$1, U13.G9
UART-TX/GPIO4: J25.2, TP33.P$1, U17.G9
UART-TX/GPIO5: J31.2, TP40.P$1, U21.G9
UART-TX/GPIO6: J37.2, TP47.P$1, U25.G9
UART-TX/GPIO7: J43.2, TP54.P$1, U29.G9
UART-TX/GPIO8: J49.2, TP61.P$1, U33.G9
UART-TX/GPIO48: J2.2, TP5.P$1, U1.G9
VDCDCRF: C4.1, R2.2, U1.G2
VDCDCRF1: C34.1, R30.2, U5.G2
VDCDCRF2: C62.1, R56.2, U9.G2
VDCDCRF3: C90.1, R82.2, U13.G2
VDCDCRF4: C118.1, R108.2, U17.G2
VDCDCRF5: C146.1, R134.2, U21.G2
VDCDCRF6: C174.1, R160.2, U25.G2
VDCDCRF7: C202.1, R186.2, U29.G2
VDCDCRF8: C230.1, R212.2, U33.G2
VDD: C12.1, C13.1, C14.1, C15.1, C16.1, C20.1, C21.1, C22.1, C25.1, C27.1, D1.C, D2.C, J3.1, J4.2, J5.1, J6.4, J6.11, M1.4, M2.4, R1.2, R3.2, R9.2, R10.2, R12.2, R13.2, R14.2, R15.2, R18.2, R23.2, R24.2, R25.1, R26.1, U1.B1, U1.B2, U1.C4, U1.F3, U1.J4, U2.2, U2.3, U2.9, U2.10, U3.1, U4.8
VDD1: C39.1, C40.1, C41.1, C42.1, C44.1, C47.1, C48.1, C49.1, C50.1, C51.1, D8.C, D9.C, J8.1, J9.4, J9.11, J10.1, J12.2, M3.4, M4.4, R27.2, R29.2, R31.2, R32.2, R33.2, R34.2, R35.2, R36.2, R42.2, R49.2, R50.2, R51.1, R52.1, U5.B1, U5.B2, U5.C4, U5.F3, U5.J4, U6.2, U6.3, U6.9, U6.10, U7.1, U8.8
VDD2: C67.1, C68.1, C69.1, C70.1, C72.1, C75.1, C76.1, C77.1, C78.1, C79.1, D15.C, D16.C, J14.1, J15.4, J15.11, J16.1, J18.2, M5.4, M6.4, R53.2, R55.2, R57.2, R58.2, R59.2, R60.2, R61.2, R62.2, R68.2, R75.2, R76.2, R77.1, R78.1, U9.B1, U9.B2, U9.C4, U9.F3, U9.J4, U10.2, U10.3, U10.9, U10.10, U11.1, U12.8
VDD3: C95.1, C96.1, C97.1, C98.1, C100.1, C103.1, C104.1, C105.1, C106.1, C107.1, D22.C, D23.C, J20.1, J21.4, J21.11, J22.1, J24.2, M7.4, M8.4, R79.2, R81.2, R83.2, R84.2, R85.2, R86.2, R87.2, R88.2, R94.2, R101.2, R102.2, R103.1, R104.1, U13.B1, U13.B2, U13.C4, U13.F3, U13.J4, U14.2, U14.3, U14.9, U14.10, U15.1, U16.8
VDD4: C123.1, C124.1, C125.1, C126.1, C128.1, C131.1, C132.1, C133.1, C134.1, C135.1, D29.C, D30.C, J26.1, J27.4, J27.11, J28.1, J30.2, M9.4, M10.4, R105.2, R107.2, R109.2, R110.2, R111.2, R112.2, R113.2, R114.2, R120.2, R127.2, R128.2, R129.1, R130.1, U17.B1, U17.B2, U17.C4, U17.F3, U17.J4, U18.2, U18.3, U18.9, U18.10, U19.1, U20.8
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
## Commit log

2018-12-18 Adding board version number
2018-12-19 Setting trace width/clearance to 5mil, via size to .2mm min
2018-12-19 Checklist cleanup of schematic.
2018-12-20 Adding 3x3 production panel and gerbers.
2019-01-28 Adding v01 of Tensorflow
2019-01-30 Adding v01 of production panel.
2019-01-30 Removing old production files (x01)
2019-02-07 Disconnecting DVDD from VDD, adding test points.
2019-02-12 Changes post-design review
    - Silkscreen on back
    - Add auto-reset diode
    - Tuck battery overpaste in under connector
2019-02-12 Adding v01 Production panel.
2019-02-12 Adding production ID's to all part numbers.
2019-02-12 Change to 100x gain with 1M ohm resistors for mics
2019-02-25 Change Mic gain to 75x
    This is Pete's requested final gain value
2019-03-05 Add generic markdown files
2019-03-05 Updating components to SparkFun ibraries
2019-03-05 Continue adding parts from SparkFun library
2019-03-05 Finish converting parts to SparkFun library
2019-05-20 Moving designators for asm sheet
2019-05-20 Adding extra ordering instruction requirements
2019-05-22 Change to module layout
2019-05-22 Moving TP to align with jig.
2019-05-22 Update silk
2019-05-22 Invert JTAG connector
2019-07-01 Add panel files
2019-07-02 Reroute camera interface to match himax spec
2019-07-03 Move MCLK to PWM pin.
2019-07-25 Move mics to 2cm spacing. Re-wire camera connection.
2019-07-25 Move cap to avoid silk
2019-07-25 Adding panel files for v2.1
2019-08-17 Change bootload circuit to use 0.1uF/220k standards.
2019-08-20 Move parts to fill gap left by DNP resistor removal. Change text in sch from Apollo3 to Artemis.
2019-09-06 Add DNP resistor back to design to match production boards.
2019-09-16 Update README.md
    I fixed a little typo on line 12
2019-09-17 Add power control via GPIO to accel and mics.
2019-09-17 Push production files before ordering protos
2019-09-19 Adding test firmware sketch for Edge v2
2019-09-20 Update for Edge 2
    - Update Readme and Links
    - Add board dimensions for Edge 2
2019-10-11 Change part ID on 0.1uF on bootload circuit
2019-10-18 Rename files. Remove dependancy on Ambiq lbr. Remove ambiq.lbr.
2019-10-18 Remove old production files.
2019-10-23 rename camera nets to reflect HM01B0 function
    This causes the schematic cymbol for the camera to look very strange b/c the pin mapping on the old (OV7670) camera was totally different. The advantage is that the functions appear at the proper loc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
2019-10-23 add gpio numbers to camera nets for ease of use
2019-10-23 label camera trigger and interrupt nets
2019-10-24 regenerate and rename schematic pdf
2019-10-28 re-assign camera pins for fast gpio compatibility
    Camera Pin : FAST GPIO Bit : Apollo3 Pad
    D0 : D0 : 24
    D1 : D1 : 33
    D2 : D2 : 10
    D3 : D3 : 11
    D4 : D4 : 28
